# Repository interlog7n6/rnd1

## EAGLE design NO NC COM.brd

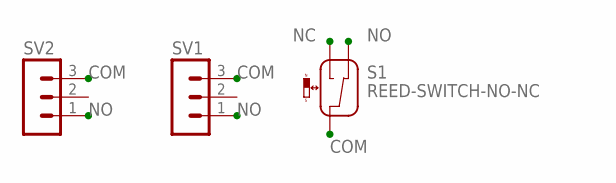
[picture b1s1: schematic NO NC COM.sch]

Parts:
S1: REED-SWITCH-NO-NC; MK6-8-C
SV1, SV2: MA03-1

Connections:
COM: S1.COM, SV1.3, SV2.3
NC: S1.NO
NO: S1.NC, SV1.1, SV2.1

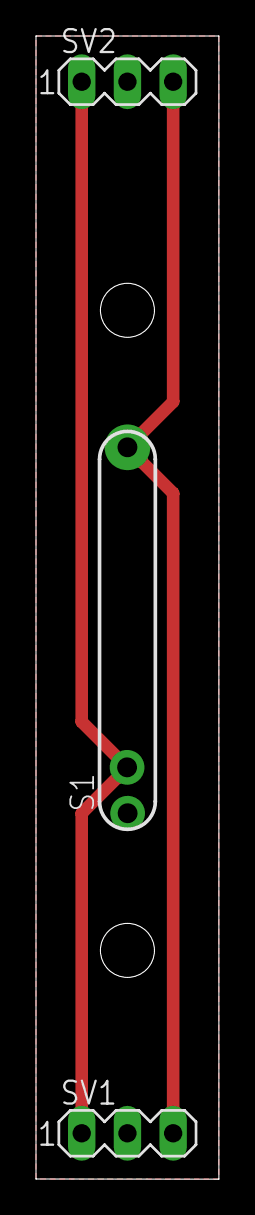
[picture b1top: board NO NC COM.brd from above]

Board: 2 copper layers, 10.2 x 63.5 mm, 3 parts (0 on the bottom side), 2 nets.
